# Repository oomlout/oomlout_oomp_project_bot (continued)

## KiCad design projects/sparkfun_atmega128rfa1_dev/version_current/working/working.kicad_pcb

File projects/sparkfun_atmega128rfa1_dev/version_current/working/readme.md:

# ATmega128RFA1_Dev by sparkfun  
This is a harvested standardized copy of a project from github.  
The original project can be found at:  
https://github.com/sparkfun/ATmega128RFA1_Dev  
Please consult that link for additional, details, files, and license information.  
Note: It was auto harvested and if the original repo had more than one board file or anything out of the ordinary the files here are likely not representative.

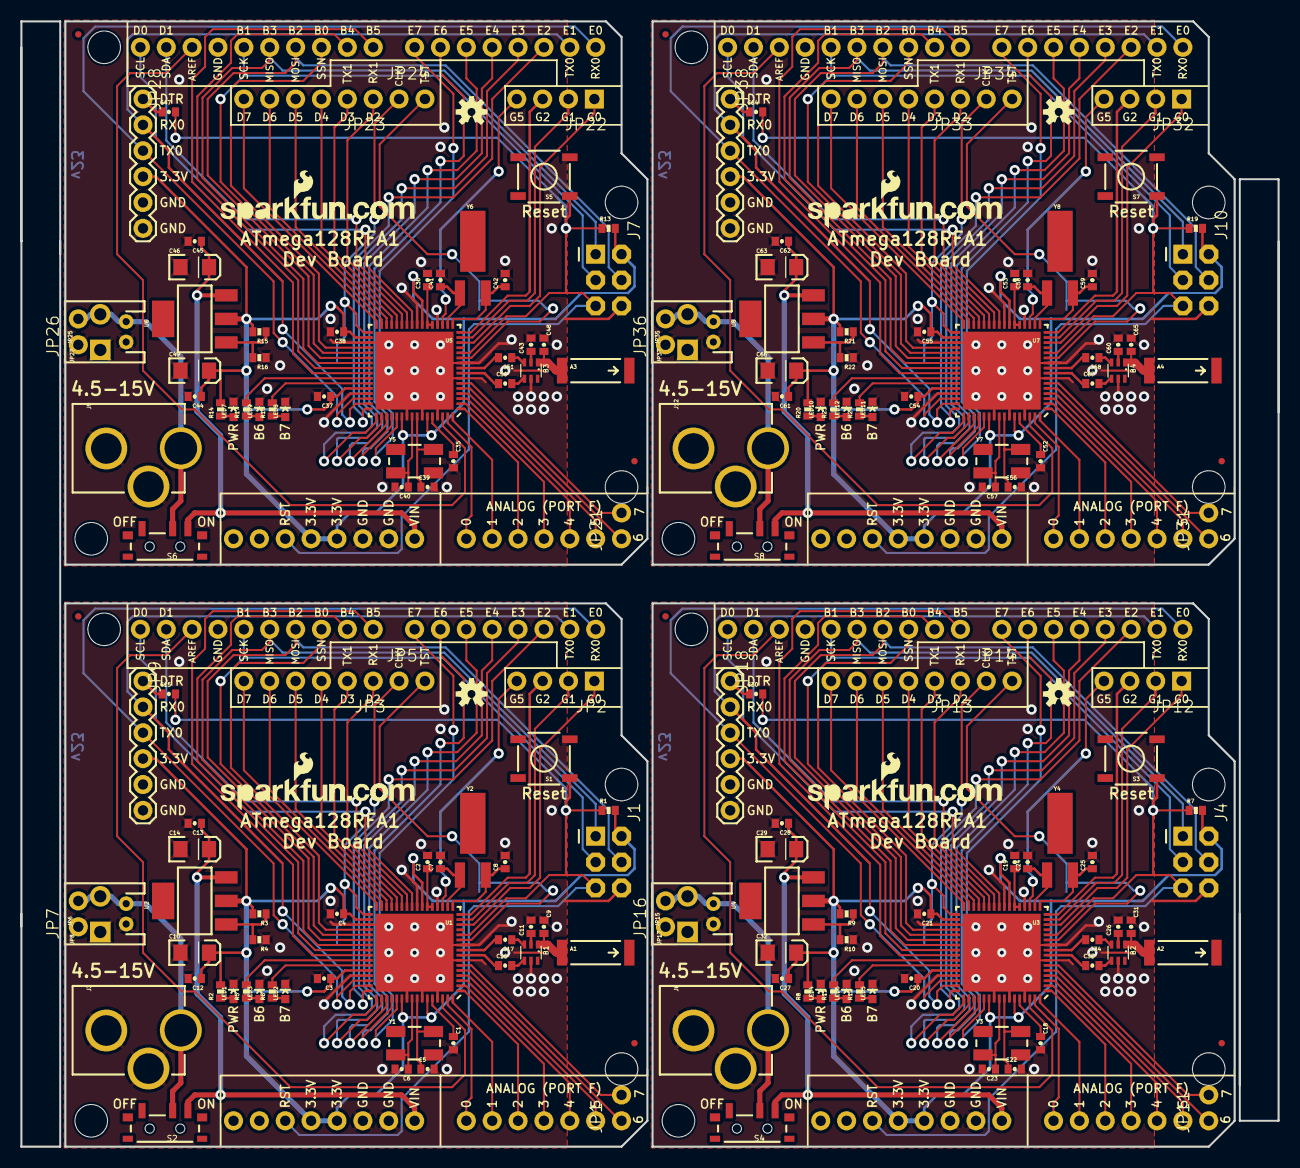
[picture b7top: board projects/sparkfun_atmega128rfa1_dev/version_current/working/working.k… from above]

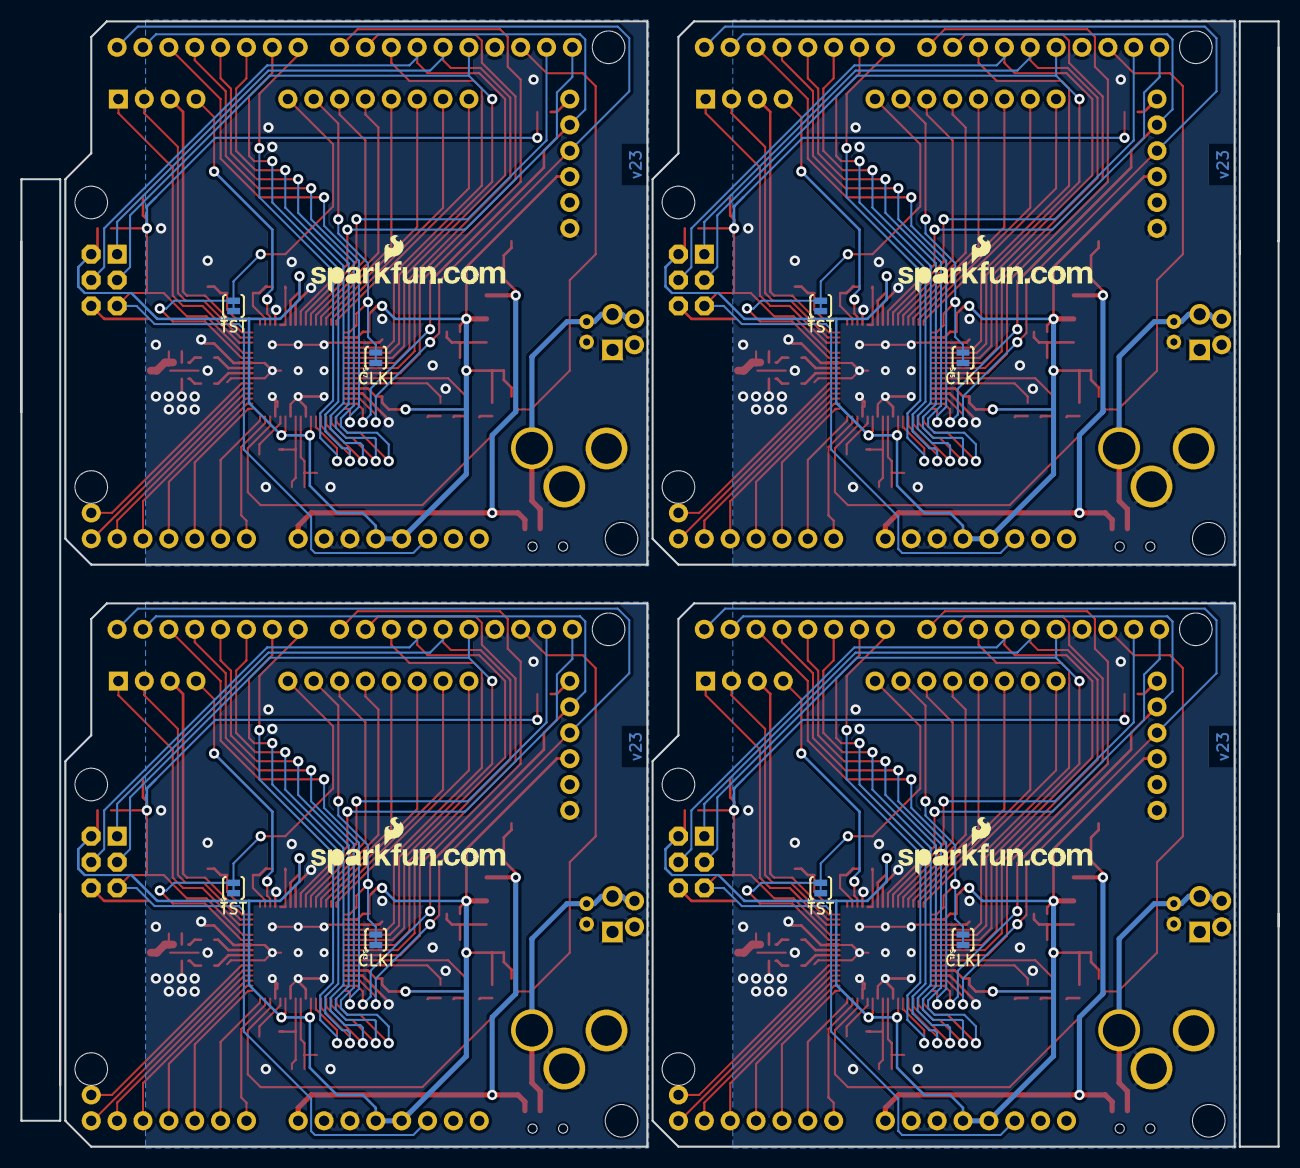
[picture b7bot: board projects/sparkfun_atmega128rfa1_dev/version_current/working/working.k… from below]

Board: 2 copper layers, 123.4 x 110.5 mm, 208 parts (12 on the bottom side), 244 nets.

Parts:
A1, A2, A3, A4: ANTENNA2SMD5; ANTENNA-CHIP5
B1, B2, B3, B4: 748421245; BALUN
C1, C2, C3, C4, C12, C18, C19, C20, C21, C27, C35, C36, C37, C38, C44, C52, C53, C54, C55, C61: 1uF; 0402-CAP
C5, C6, C7, C8, C22, C23, C24, C25, C39, C40, C41, C42, C56, C57, C58, C59: 12pF; 0402-CAP
C9, C31, C48, C65: 0.75pF; 0402-CAP
C10, C14, C29, C32, C46, C49, C63, C66: 10uF; EIA3216
C11, C26, C43, C60: 22pF; 0402-CAP
C13, C15, C28, C30, C45, C47, C62, C64: 0.1uF; 0402-CAP
C16, C17, C33, C34, C50, C51, C67, C68: JUMP; 0402-CAP
FID1, FID2, FID3, FID4, FID5, FID6, FID7, FID8: FIDUCIALUFIDUCIAL; MICRO-FIDUCIAL
J1, J4, J7, J10: ISP; 2X3-NS
J2, J5, J8, J11: ARDUINO_UNO_R3
J3, J6, J9, J12: POWER_JACKPTH_LOCK; POWER_JACK_PTH_LOCK
JP1, JP5, JP7, JP11, JP14, JP16, JP21, JP24, JP26, JP31, JP34, JP36: 1X02_NO_SILK
JP2, JP12, JP22, JP32: 1X04_NO_SILK
JP3, JP13, JP23, JP33: 1X06_NS
JP4, JP10, JP19, JP20, JP29, JP30, JP39, JP40: LOGO-SFENEW; SFE-NEW-WEBLOGO
JP6, JP15, JP25, JP35: JST-2-PTH
JP8, JP17, JP27, JP37: SCREWTERMINAL-3.5MM-2-NS
JP9, JP18, JP28, JP38: FTDI; FTDI_BASIC
LED1, LED4, LED7, LED10: RED; LED-0603
LED2, LED3, LED5, LED6, LED8, LED9, LED11, LED12: GREEN; LED-0603
R1, R7, R13, R19: 10k; 0402-RES
R2, R8, R14, R20: 1k; 0402-RES
R3, R9, R15, R21: 240; 0402-RES
R4, R10, R16, R22: 390; 0402-RES
R5, R6, R11, R12, R17, R18, R23, R24: 330; 0402-RES
S1, S3, S5, S7: TACTILE_SWITCH_SMD
S2, S4, S6, S8: SWITCH-SPST-SMD-A
SJ1, SJ2, SJ3, SJ4, SJ5, SJ6, SJ7, SJ8: SJ_2S-TRACE
U1, U3, U5, U7: ATMEGA128RFA1; QFN-64
U2, U4, U6, U8: LM1117; SOT223
U$1, U$2, U$3, U$4: OSHW-LOGOS; OSHW-LOGO-S
Y1, Y3, Y5, Y7: 16MHz; CRYSTAL-SMD-5X3
Y2, Y4, Y6, Y8: 32.768kHz; CRYSTAL-32KHZ-SMD

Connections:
3.3V: C3.1, C4.1, C10.A, C12.1, J1.2, J2.3.3V, J2.5V, JP9.VCC, R1.2, R2.2, R3.2, U1.23, U1.34, U1.44, U1.54, U1.59, U2.2
3.3V1: C20.1, C21.1, C27.1, C32.A, J4.2, J5.3.3V, J5.5V, JP18.VCC, R7.2, R8.2, R9.2, U3.23, U3.34, U3.44, U3.54, U3.59, U4.2
3.3V2: C37.1, C38.1, C44.1, C49.A, J7.2, J8.3.3V, J8.5V, JP28.VCC, R13.2, R14.2, R15.2, U5.23, U5.34, U5.44, U5.54, U5.59, U6.2
3.3V3: C54.1, C55.1, C61.1, C66.A, J10.2, J11.3.3V, J11.5V, JP38.VCC, R19.2, R20.2, R21.2, U7.23, U7.34, U7.44, U7.54, U7.59, U8.2
A0: J2.A0, U1.63
A1: J2.A1, U1.64
A2: J2.A2, U1.1
A3: J2.A3, U1.2
A4: J2.A4, U1.3
A5: J2.A5, U1.4
A6: JP1.1, U1.5
A7: JP1.2, U1.6
A8: J5.A0, U3.63
A9: J5.A1, U3.64
A10: J5.A2, U3.1
A11: J5.A3, U3.2
A12: J5.A4, U3.3
A13: J5.A5, U3.4
A14: JP11.1, U3.5
A15: JP11.2, U3.6
A16: J8.A0, U5.63
A17: J8.A1, U5.64
A18: J8.A2, U5.1
A19: J8.A3, U5.2
A20: J8.A4, U5.3
A21: J8.A5, U5.4
A22: JP21.1, U5.5
A23: JP21.2, U5.6
A24: J11.A0, U7.63
A25: J11.A1, U7.64
A26: J11.A2, U7.1
A27: J11.A3, U7.2
A28: J11.A4, U7.3
A29: J11.A5, U7.4
A30: JP31.1, U7.5
A31: JP31.2, U7.6
AREF: J2.AREF, U1.62
AREF1: J5.AREF, U3.62
AREF2: J8.AREF, U5.62
AREF3: J11.AREF, U7.62
AVDD: C1.1, U1.60
AVDD1: C18.1, U3.60
AVDD2: C35.1, U5.60
AVDD3: C52.1, U7.60
CLKI: JP5.1, SJ1.2, U1.33
CLKI1: JP14.1, SJ3.2, U3.33
CLKI2: JP24.1, SJ5.2, U5.33
CLKI3: JP34.1, SJ7.2, U7.33
DTR: C15.1, JP9.DTR
DTR1: C30.1, JP18.DTR
DTR2: C47.1, JP28.DTR
DTR3: C64.1, JP38.DTR
DVDD: C2.1, U1.21, U1.22
DVDD1: C19.1, U3.21, U3.22
DVDD2: C36.1, U5.21, U5.22
DVDD3: C53.1, U7.21, U7.22
FB: R3.1, R4.2, U2.1
FB1: R9.1, R10.2, U4.1
FB2: R15.1, R16.2, U6.1
FB3: R21.1, R22.2, U8.1
GND: B1.5, C1.2, C2.2, C3.2, C4.2, C5.2, C6.2, C7.2, C8.2, C9.1, C10.C, C11.2, C12.2, C13.2, C14.C, J1.6, J2.GND@0, J2.GND@1, J2.GND@2, J3.GND, J3.GNDBREAK, JP6.1, JP7.1, JP8.1, JP9.GND, LED1.C, LED2.C, LED3.C, R4.1, S1.3, SJ1.1, SJ2.1, U1.7, U1.10, U1.20, U1.24, U1.35, U1.45, U1.55, U1.58, U1.61, U1.65
GND1: B2.5, C18.2, C19.2, C20.2, C21.2, C22.2, C23.2, C24.2, C25.2, C26.2, C27.2, C28.2, C29.C, C31.1, C32.C, J4.6, J5.GND@0, J5.GND@1, J5.GND@2, J6.GND, J6.GNDBREAK, JP15.1, JP16.1, JP17.1, JP18.GND, LED4.C, LED5.C, LED6.C, R10.1, S3.3, SJ3.1, SJ4.1, U3.7, U3.10, U3.20, U3.24, U3.35, U3.45, U3.55, U3.58, U3.61, U3.65
GND2: B3.5, C35.2, C36.2, C37.2, C38.2, C39.2, C40.2, C41.2, C42.2, C43.2, C44.2, C45.2, C46.C, C48.1, C49.C, J7.6, J8.GND@0, J8.GND@1, J8.GND@2, J9.GND, J9.GNDBREAK, JP25.1, JP26.1, JP27.1, JP28.GND, LED7.C, LED8.C, LED9.C, R16.1, S5.3, SJ5.1, SJ6.1, U5.7, U5.10, U5.20, U5.24, U5.35, U5.45, U5.55, U5.58, U5.61, U5.65
GND3: B4.5, C52.2, C53.2, C54.2, C55.2, C56.2, C57.2, C58.2, C59.2, C60.2, C61.2, C62.2, C63.C, C65.1, C66.C, J10.6, J11.GND@0, J11.GND@1, J11.GND@2, J12.GND, J12.GNDBREAK, JP35.1, JP36.1, JP37.1, JP38.GND, LED10.C, LED11.C, LED12.C, R22.1, S7.3, SJ7.1, SJ8.1, U7.7, U7.10, U7.20, U7.24, U7.35, U7.45, U7.55, U7.58, U7.61, U7.65
MISO: J1.1, J2.D12, U1.39
MISO1: J4.1, J5.D12, U3.39
MISO2: J7.1, J8.D12, U5.39
MISO3: J10.1, J11.D12, U7.39
MOSI: J1.4, J2.D11, U1.38
MOSI1: J4.4, J5.D11, U3.38
MOSI2: J7.4, J8.D11, U5.38
MOSI3: J10.4, J11.D11, U7.38
unnamed: C22.1, U3.57, Y3.3
unnamed: LED1.A, R2.1
unnamed: C5.1, U1.57, Y1.3
unnamed: C6.1, U1.56, Y1.1
unnamed: C7.1, U1.18, Y2.X1
unnamed: C8.1, U1.17, Y2.X2
unnamed: B1.2, C11.1
unnamed: LED3.A, R5.1
unnamed: J3.PWR, JP6.2, JP7.2, JP8.2, S2.2
unnamed: B1.4, C16.2
unnamed: B1.3, C17.1
unnamed: C23.1, U3.56, Y3.1
unnamed: LED2.A, R6.1
unnamed: C24.1, U3.18, Y4.X1
unnamed: C25.1, U3.17, Y4.X2
unnamed: LED4.A, R8.1
unnamed: B2.2, C26.1
unnamed: B2.4, C33.2
unnamed: B2.3, C34.1
unnamed: LED6.A, R11.1
unnamed: LED5.A, R12.1
unnamed: J6.PWR, JP15.2, JP16.2, JP17.2, S4.2
unnamed: C39.1, U5.57, Y5.3
unnamed: C40.1, U5.56, Y5.1
unnamed: C41.1, U5.18, Y6.X1
unnamed: C42.1, U5.17, Y6.X2
unnamed: LED7.A, R14.1
unnamed: B3.2, C43.1
unnamed: B3.4, C50.2
unnamed: B3.3, C51.1
unnamed: LED9.A, R17.1
unnamed: LED8.A, R18.1
unnamed: J9.PWR, JP25.2, JP26.2, JP27.2, S6.2
unnamed: C56.1, U7.57, Y7.3
unnamed: C57.1, U7.56, Y7.1
unnamed: C58.1, U7.18, Y8.X1
unnamed: C59.1, U7.17, Y8.X2
unnamed: LED10.A, R20.1
unnamed: B4.2, C60.1
unnamed: B4.4, C67.2
unnamed: B4.3, C68.1
unnamed: LED12.A, R23.1
unnamed: LED11.A, R24.1
unnamed: J12.PWR, JP35.2, JP36.2, JP37.2, S8.2
PB1: R12.2, U3.43
PB2: R11.2, U3.42
PB3: J5.D8, U3.41
PB4: J2.D9, U1.40
PB5: J2.D8, U1.41
PB6: R5.2, U1.42
PB7: R6.2, U1.43
PB8: J5.D9, U3.40
PB9: R18.2, U5.43
PB10: R17.2, U5.42
PB11: J8.D8, U5.41
PB12: J8.D9, U5.40
PB13: R24.2, U7.43
PB14: R23.2, U7.42
PB15: J11.D8, U7.41
PB16: J11.D9, U7.40
PD1: JP13.6, U3.32
PD2: JP13.5, U3.31
PD3: JP13.4, U3.30
PD4: JP3.3, U1.29
PD5: JP3.4, U1.30
PD6: JP3.5, U1.31
PD7: JP3.6, U1.32
PD8: JP13.3, U3.29
PD9: JP23.6, U5.32
PD10: JP23.5, U5.31
PD11: JP23.4, U5.30
PD12: JP23.3, U5.29
PD13: JP33.6, U7.32
PD14: JP33.5, U7.31
PD15: JP33.4, U7.30
PD16: JP33.3, U7.29
PE1: J5.D7, U3.53
PE2: J2.D2, U1.48
PE3: J2.D3, U1.49
PE4: J2.D4, U1.50
PE5: J2.D5, U1.51
PE6: J2.D6, U1.52
PE7: J2.D7, U1.53
PE8: J5.D6, U3.52
PE9: J5.D5, U3.51
PE10: J5.D4, U3.50
PE11: J5.D3, U3.49
PE12: J5.D2, U3.48
PE13: J8.D7, U5.53
PE14: J8.D6, U5.52
PE15: J8.D5, U5.51
PE16: J8.D4, U5.50
PE17: J8.D3, U5.49
PE18: J8.D2, U5.48
PE19: J11.D7, U7.53
PE20: J11.D6, U7.52
PE21: J11.D5, U7.51
PE22: J11.D4, U7.50
PE23: J11.D3, U7.49
PE24: J11.D2, U7.48
PG0: JP2.1, U1.14
PG1: JP2.2, U1.15
PG2: JP2.3, U1.16
PG3: JP12.4, U3.19
PG4: JP12.3, U3.16
PG5: JP2.4, U1.19
PG6: JP12.2, U3.15
PG7: JP12.1, U3.14
PG8: JP22.4, U5.19
PG9: JP22.3, U5.16
PG10: JP22.2, U5.15
PG11: JP22.1, U5.14
PG12: JP32.4, U7.19
PG13: JP32.3, U7.16
PG14: JP32.2, U7.15
PG15: JP32.1, U7.14
RESET: C15.2, J1.5, J2.RES, R1.1, S1.1, U1.12
RESET1: C30.2, J4.5, J5.RES, R7.1, S3.1, U3.12
RESET2: C47.2, J7.5, J8.RES, R13.1, S5.1, U5.12
RESET3: C64.2, J10.5, J11.RES, R19.1, S7.1, U7.12
RFANT: A1.FEED, B1.1, C9.2
RFANT1: A2.FEED, B2.1, C31.2
RFANT2: A3.FEED, B3.1, C48.2
RFANT3: A4.FEED, B4.1, C65.2
RFN: C17.2, U1.9
RFN1: C34.2, U3.9
RFN2: C51.2, U5.9
RFN3: C68.2, U7.9
RFP: C16.1, U1.8
RFP1: C33.1, U3.8
RFP2: C50.1, U5.8
RFP3: C67.1, U7.8
RX0: J2.RX, JP9.TXO, U1.46
RX1: JP3.1, U1.27
RX2: J5.RX, JP18.TXO, U3.46
RX3: JP13.1, U3.27
RX4: J8.RX, JP28.TXO, U5.46
RX5: JP23.1, U5.27
RX6: J11.RX, JP38.TXO, U7.46
RX7: JP33.1, U7.27
SCK: J1.3, J2.D13, U1.37
SCK1: J4.3, J5.D13, U3.37
SCK2: J7.3, J8.D13, U5.37
SCK3: J10.3, J11.D13, U7.37
SCL: J2.SCL, U1.25
SCL1: J5.SCL, U3.25
SCL2: J8.SCL, U5.25
SCL3: J11.SCL, U7.25
SDA: J2.SDA, U1.26
SDA1: J5.SDA, U3.26
SDA2: J8.SDA, U5.26
SDA3: J11.SDA, U7.26
SSN: J2.D10, U1.36
SSN1: J5.D10, U3.36
SSN2: J8.D10, U5.36
SSN3: J11.D10, U7.36
TST: JP5.2, SJ2.2, U1.11
TST1: JP14.2, SJ4.2, U3.11
TST2: JP24.2, SJ6.2, U5.11
TST3: JP34.2, SJ8.2, U7.11
TX0: J2.TX, JP9.RXI, U1.47
TX1: JP3.2, U1.28
TX2: J5.TX, JP18.RXI, U3.47
TX3: JP13.2, U3.28
TX4: J8.TX, JP28.RXI, U5.47
TX5: JP23.2, U5.28
TX6: J11.TX, JP38.RXI, U7.47
TX7: JP33.2, U7.28
VCC: C13.1, C14.A, J2.VIN, S2.1, U2.3
VCC1: C28.1, C29.A, J5.VIN, S4.1, U4.3
VCC2: C45.1, C46.A, J8.VIN, S6.1, U6.3
VCC3: C62.1, C63.A, J11.VIN, S8.1, U8.3

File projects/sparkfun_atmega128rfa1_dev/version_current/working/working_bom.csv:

Row,Description,Part,References,Value,Footprint,Quantity Per PCB,Status,Datasheet
1,,ANTENNA2SMD5,A1,ANTENNA2SMD5,ANTENNA-CHIP5,1, ,
2,,BALUN0805,B1,BALUN0805,BALUN,1, ,
3,,CAP0402-CAP,C9,0.75pF,0402-CAP,1, ,
4,,CAP0402-CAP,C5 C6 C7 C8,12pF,0402-CAP,4, ,
5,,CAP0402-CAP,C11,22pF,0402-CAP,1, ,
6,,CAP0402-CAP,C13 C15,0.1uF,0402-CAP,2, ,
7,,CAP0402-CAP,C1 C2 C3 C4 C12,1uF,0402-CAP,5, ,
8,,CAP_POL1206,C10 C14,10uF,EIA3216,2, ,
9,,SparkFun_CAP0402-CAP,C16 C17,JUMP,0402-CAP,2, ,
10,,ARDUINO_UNO_R3,J2,ARDUINO_UNO_R3,ARDUINO_UNO_R3,1, ,
11,,AVR_SPI_PRG_6NS,J1,AVR_SPI_PRG_6NS,2X3-NS,1, ,
12,,POWER_JACKPTH_LOCK,J3,POWER_JACKPTH_LOCK,POWER_JACK_PTH_LOCK,1, ,
13,,FTDI_BASICPTH,JP9,FTDI_BASICPTH,FTDI_BASIC,1, ,
14,,LOGO-SFENEW,JP4 JP10,LOGO-SFENEW,SFE-NEW-WEBLOGO,2, ,
15,,M021X02_NO_SILK,JP1 JP5 JP7,M021X02_NO_SILK,1X02_NO_SILK,3, ,
16,,M023.5MM-NO_SILK,JP8,M023.5MM-NO_SILK,SCREWTERMINAL-3.5MM-2-NS,1, ,
17,,M02JST-PTH-2,JP6,M02JST-PTH-2,JST-2-PTH,1, ,
18,,M041X04_NO_SILK,JP2,M041X04_NO_SILK,1X04_NO_SILK,1, ,
19,,M06SIP-NS,JP3,M06SIP-NS,1X06_NS,1, ,
20,,LED0603,LED2 LED3,GREEN,LED-0603,2, ,
21,,LED0603,LED1,RED,LED-0603,1, ,
22,,SparkFun_RESISTOR0402-RES,R3,240,0402-RES,1, ,
23,,SparkFun_RESISTOR0402-RES,R5 R6,330,0402-RES,2, ,
24,,SparkFun_RESISTOR0402-RES,R4,390,0402-RES,1, ,
25,,RESISTOR0402-RES,R2,1k,0402-RES,1, ,
26,,RESISTOR0402-RES,R1,10k,0402-RES,1, ,
27,,SWITCH-MOMENTARY-2SMD,S1,SWITCH-MOMENTARY-2SMD,TACTILE_SWITCH_SMD,1, ,
28,,SWITCH-SPST-SMD-A,S2,SWITCH-SPST-SMD-A,SWITCH-SPST-SMD-A,1, ,
29,,ATMEGA128RFA1,U1,ATMEGA128RFA1,QFN-64,1, ,
30,,V_REG_317SMD,U2,V_REG_317SMD,SOT223,1, ,
31,,OSHW-LOGOS,U$1,OSHW-LOGOS,OSHW-LOGO-S,1, ,
32,,CRYSTAL5X3,Y1,16MHz,CRYSTAL-SMD-5X3,1, ,
33,,CRYSTAL32-SMD,Y2,32.768kHz,CRYSTAL-32KHZ-SMD,1, ,





Project info:
Schematic:,working
Variant:,default
Revision:,
Date:,2023-08-06_12-55-58
KiCad Version:,7.0.6-7.0.6~ubuntu22.04.1
Statistics:
Component Groups:,33
Component Count:,48 (0 SMD/ 0 THT)
Fitted Components:,48 (0 SMD/ 0 THT)
Number of PCBs:,1
Total Components:,48

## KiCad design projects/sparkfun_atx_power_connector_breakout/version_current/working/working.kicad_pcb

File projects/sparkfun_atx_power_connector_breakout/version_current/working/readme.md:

# OOMP Project  
## ATX_Power_Connector_Breakout  by sparkfun  
  
oomp key: oomp_projects_flat_sparkfun_atx_power_connector_breakout  
(snippet of original readme)  
  
SparkFun ATX Power Connector Breakout - 12V/5V (4-pin)  
========================================  
  
<table class="table table-hover table-striped table-bordered">  
  <tr align="center">  
   <td></td>  
   <td></td>  
  </tr>  
  <tr align="center">  
    <td><i>SparkFun ATX Power Connector Breakout - 12V/5V (4-pin) <a href="https://www.sparkfun.com/products/15035">(BOB-15035)</a></i></td>  
    <td><i>SparkFun ATX Power Connector Breakout Kit - 12V/5V (4-pin) <a href="https://www.sparkfun.com/products/15701">(KIT-15701)</a></i></td>  
  </tr>  
</table>  
  
Do you need to power a project with 12V and 5V from one power supply? The ATX power connector breakout board breaks out the standard 4-pin computer peripheral port when mated with an ATX connector [(PRT-15700)](https://www.sparkfun.com/products/15700) for your 12V and 5V devices! Once you have chosen a power supply (whether it be an ATX power supply or the 12V/5V wall adapter), you're ready to give your project some life! This kit has everything you need (including a 12V/5  
  full source readme at [readme_src.md](readme_src.md)  
  
source repo at: [https://github.com/sparkfun/ATX_Power_Connector_Breakout](https://github.com/sparkfun/ATX_Power_Connector_Breakout)  
## Board  

## Schematic  

[schematic pdf](working_schematic.pdf)  
## Images

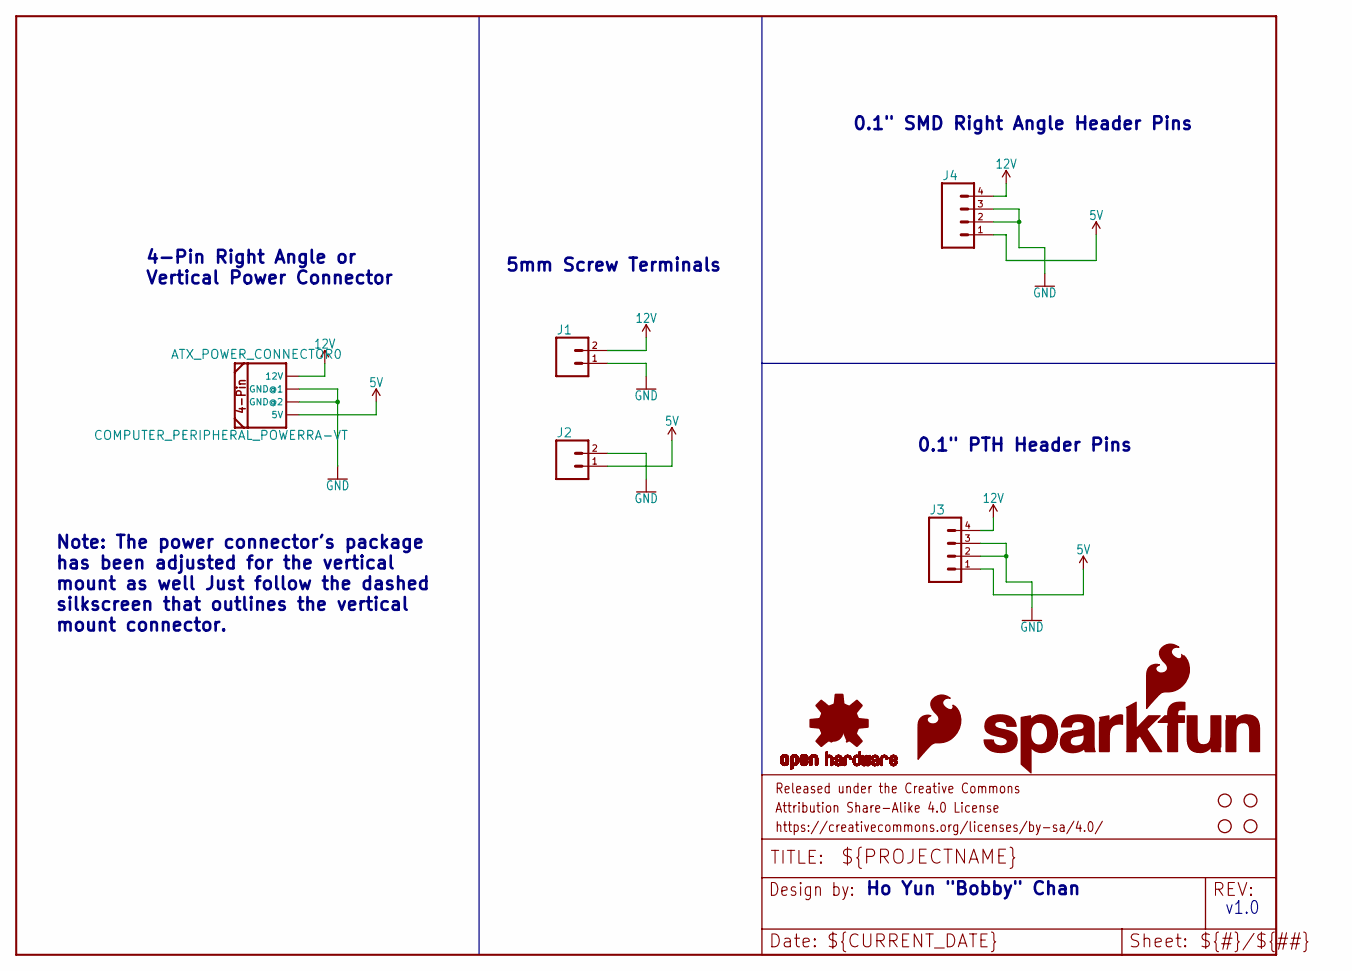
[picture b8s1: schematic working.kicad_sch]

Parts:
ATX_POWER_CONNECTOR0: COMPUTER_PERIPHERAL_POWERRA-VT; COMPUTER-PERIPHERAL-POWER-RA-VT
FRAME1: FRAME-LETTER; CREATIVE_COMMONS
H1, H2, H3, H4: STAND-OFF
J1, J2: CONN_025MM; SCREWTERMINAL-5MM-2
J3: CONN_04; 1X04
J4: CONN_04SMD; 1X04_SMD_RA_MALE
LOGO1: OSHW-LOGOS; OSHW-LOGO-S
LOGO2: SFE_LOGO_NAME_FLAME.1_INCH; SFE_LOGO_NAME_FLAME_.1
LOGO3: SFE_LOGO_FLAME.1_INCH; SFE_LOGO_FLAME_.1

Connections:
5V: ATX_POWER_CONNECTOR0.5V, J2.1, J3.1, J4.1
12V: ATX_POWER_CONNECTOR0.12V, J1.2, J3.4, J4.4
GND: ATX_POWER_CONNECTOR0.GND@1 (GND@2), ATX_POWER_CONNECTOR0.GND@2 (GND@1), J1.1, J2.2, J3.2, J3.3, J4.2, J4.3

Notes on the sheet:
0.1" SMD Right Angle Header Pins
4-Pin Right Angle or Vertical Power Connector
0.1" PTH Header Pins
v1.0
5mm Screw Terminals
Note: The power connector's package has been adjusted for the vertical mount as well~{} Just follow the dashed silkscreen that outlines the vertical mount connector.
Ho Yun "Bobby" Chan

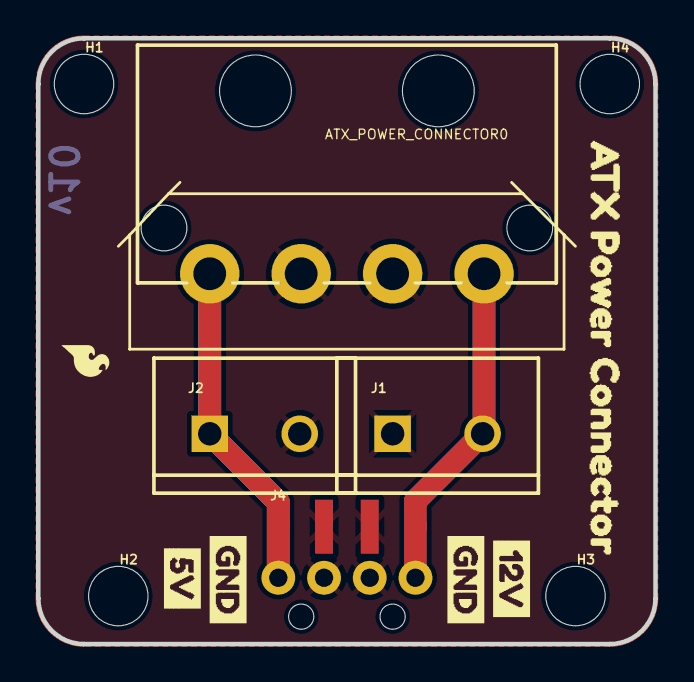
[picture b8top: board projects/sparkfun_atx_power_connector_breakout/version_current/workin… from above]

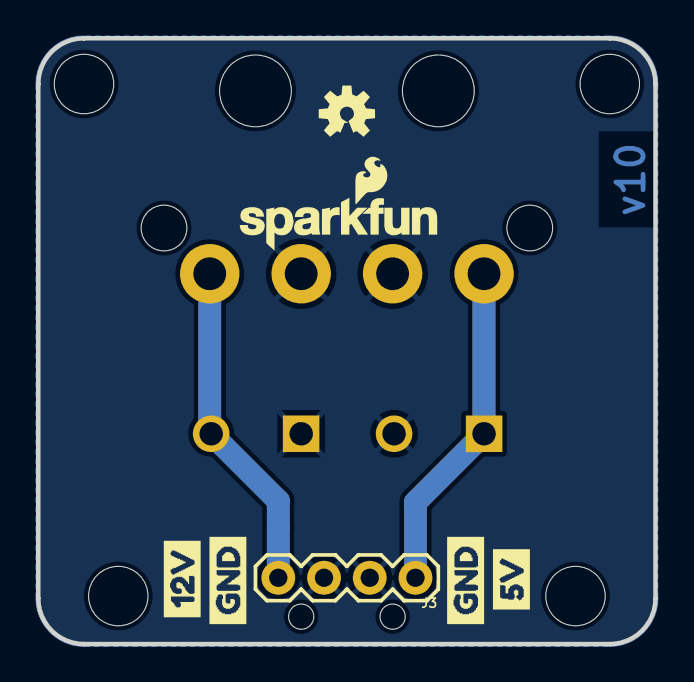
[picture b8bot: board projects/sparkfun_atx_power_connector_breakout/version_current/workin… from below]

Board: 2 copper layers, 34.3 x 33.7 mm, 22 parts (7 on the bottom side), 3 nets.

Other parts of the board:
U$1, U$5: 12V0
U$2, U$8: 5V0
U$3, U$4, U$6, U$7: GND0
U$9: ATX_POWER_CONNECTOR0
